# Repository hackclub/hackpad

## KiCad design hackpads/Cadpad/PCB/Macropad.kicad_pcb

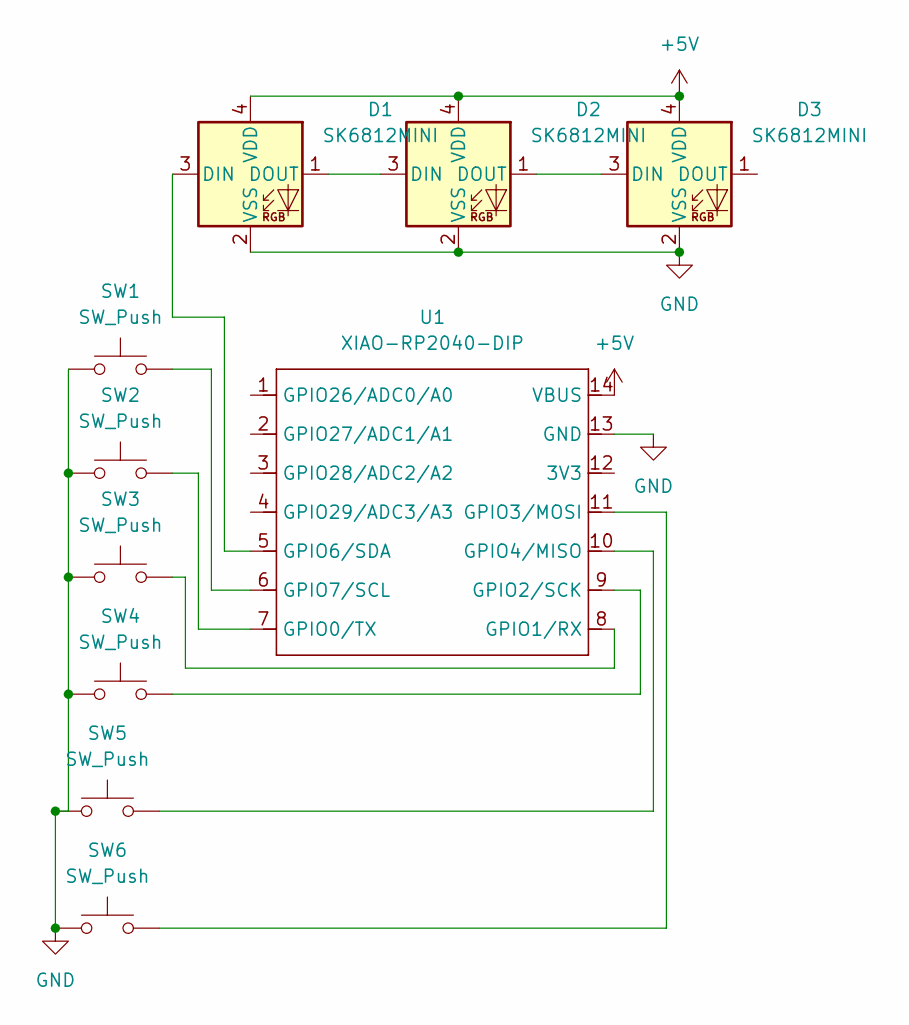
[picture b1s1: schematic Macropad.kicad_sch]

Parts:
D1, D2, D3: SK6812MINI; LED_SK6812MINI_PLCC4_3.5x3.5mm_P1.75mm
SW1, SW2, SW3, SW4, SW5, SW6: SW_Push; SW_Cherry_MX_1.00u_PCB
U1: XIAO-RP2040-DIP

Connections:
+5V: D1.4 (VDD), D2.4 (VDD), D3.4 (VDD), U1.14 (VBUS)
GND: D1.2 (VSS), D2.2 (VSS), D3.2 (VSS), SW1.1, SW2.1, SW3.1, SW4.1, SW5.1, SW6.1, U1.13 (GND)
unnamed: D1.3 (DIN), U1.5 (GPIO6/SDA)
unnamed: D1.1 (DOUT), D2.3 (DIN)
unnamed: D2.1 (DOUT), D3.3 (DIN)
unnamed: SW2.2, U1.7 (GPIO0/TX)
unnamed: SW3.2, U1.8 (GPIO1/RX)
unnamed: SW4.2, U1.9 (GPIO2/SCK)
unnamed: SW6.2, U1.11 (GPIO3/MOSI)
unnamed: SW5.2, U1.10 (GPIO4/MISO)
unnamed: SW1.2, U1.6 (GPIO7/SCL)

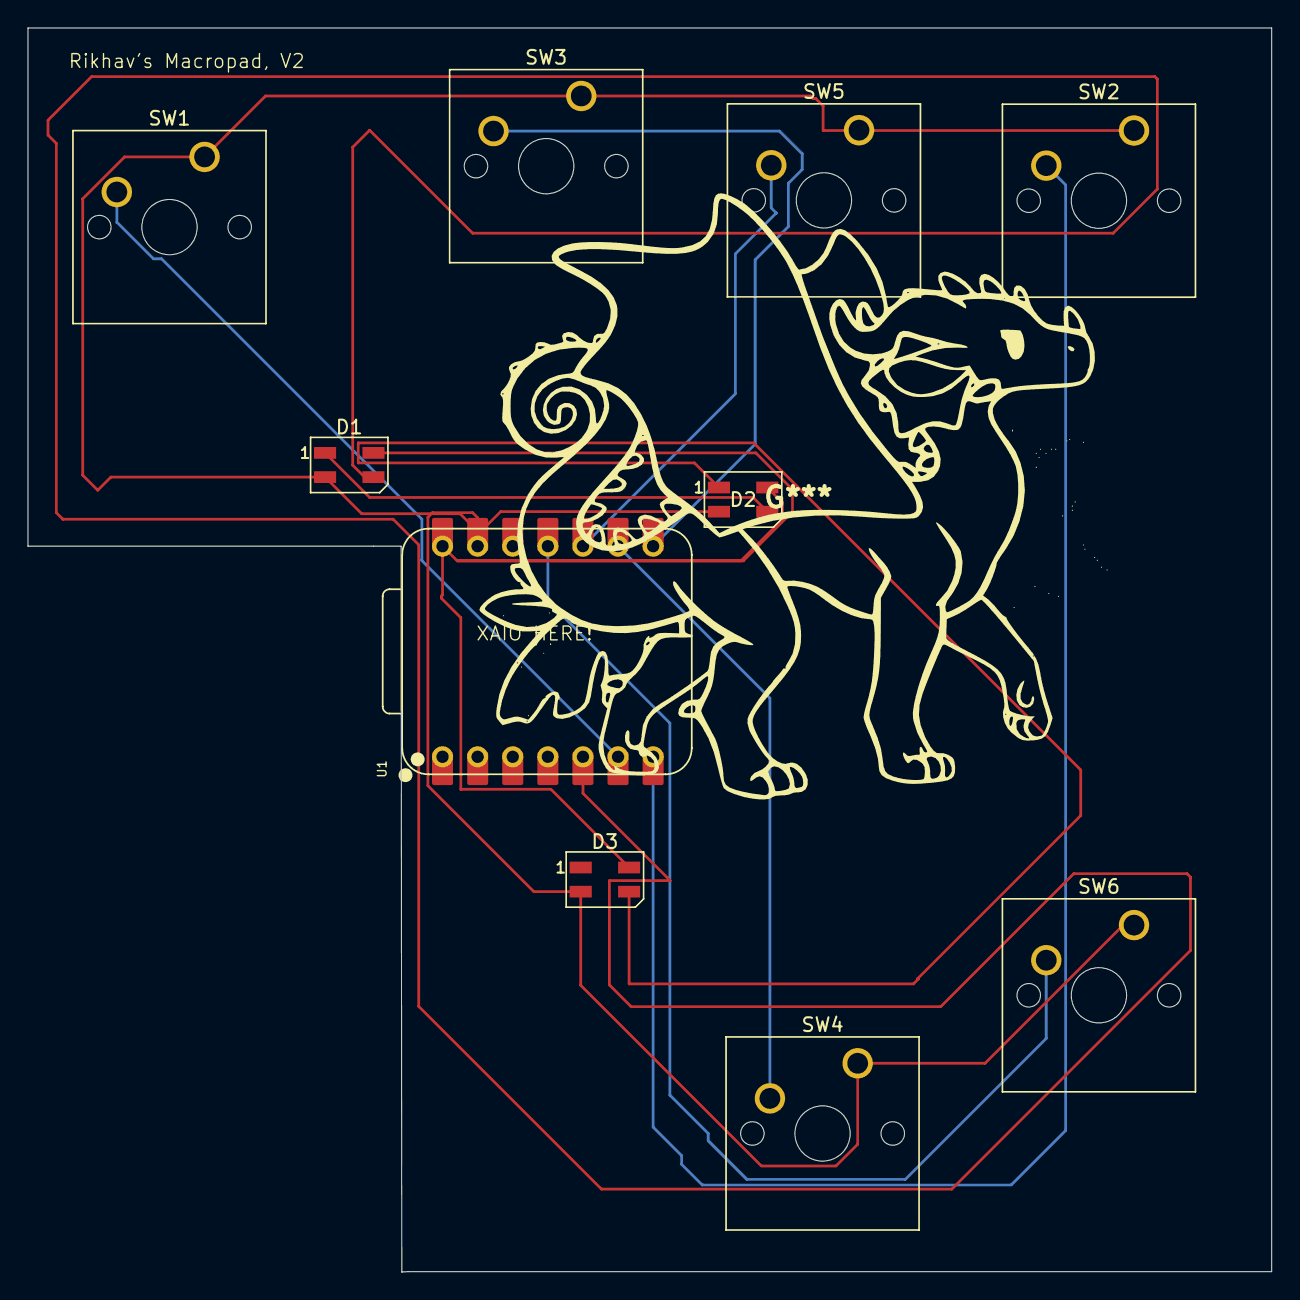
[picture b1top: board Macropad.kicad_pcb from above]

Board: 2 copper layers, 90.0 x 90.0 mm, 10 parts (0 on the bottom side), 11 nets.

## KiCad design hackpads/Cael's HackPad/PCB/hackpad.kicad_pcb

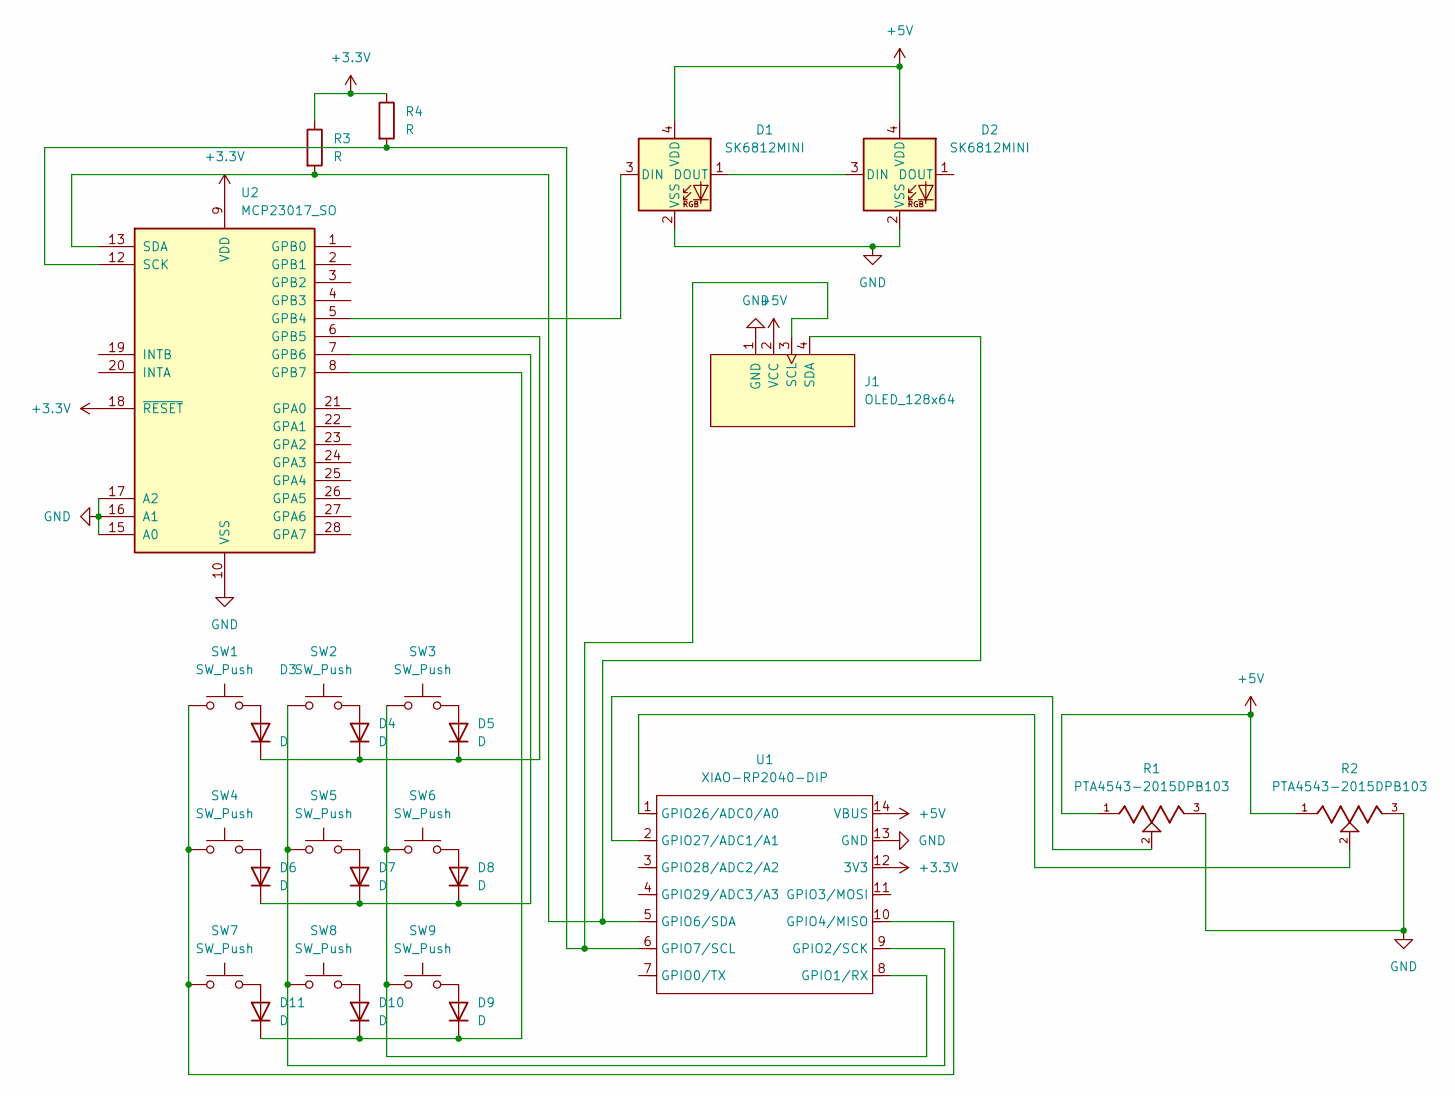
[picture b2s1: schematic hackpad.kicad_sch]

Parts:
D1, D2: SK6812MINI; LED_SK6812MINI_PLCC4_3.5x3.5mm_P1.75mm
D3, D4, D5, D6, D7, D8, D9, D10, D11: D; D_DO-35_SOD27_P7.62mm_Horizontal
J1: OLED_128x64; Adafruit_SSD1306
R1, R2: PTA4543-2015DPB103; BOURNS-PTA4543_45mm-slide-pot; PARTREV 04/21
R3, R4: R; R_Axial_DIN0204_L3.6mm_D1.6mm_P7.62mm_Horizontal
SW1, SW2, SW3, SW4, SW5, SW6, SW7, SW8, SW9: SW_Push; SW_Cherry_MX_1.00u_PCB
U1: XIAO-RP2040-DIP
U2: MCP23017_SO; SOIC-28W_7.5x17.9mm_P1.27mm

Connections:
+3.3V: R3.1, R4.1, U1.12 (3V3), U2.9 (VDD), U2.18 (~RESET)
+5V: D1.4 (VDD), D2.4 (VDD), J1.2 (VCC), R1.1, R2.1, U1.14 (VBUS)
GND: D1.2 (VSS), D2.2 (VSS), J1.1 (GND), R1.3, R2.3, U1.13 (GND), U2.10 (VSS), U2.15 (A0), U2.16 (A1), U2.17 (A2)
unnamed: D1.3 (DIN), U2.5 (GPB4)
unnamed: D1.1 (DOUT), D2.3 (DIN)
unnamed: D3.2 (A), SW1.2
unnamed: D3.1 (K), D4.1 (K), D5.1 (K), U2.6 (GPB5)
unnamed: D4.2 (A), SW2.2
unnamed: D5.2 (A), SW3.2
unnamed: D6.2 (A), SW4.2
unnamed: D6.1 (K), D7.1 (K), D8.1 (K), U2.7 (GPB6)
unnamed: D7.2 (A), SW5.2
unnamed: D8.2 (A), SW6.2
unnamed: D9.2 (A), SW9.2
unnamed: D10.2 (A), SW8.2
unnamed: D9.1 (K), D10.1 (K), D11.1 (K), U2.8 (GPB7)
unnamed: D11.2 (A), SW7.2
unnamed: J1.3 (SCL), R4.2, U1.6 (GPIO7/SCL), U2.12 (SCK)
unnamed: J1.4 (SDA), R3.2, U1.5 (GPIO6/SDA), U2.13 (SDA)
unnamed: SW3.1, SW6.1, SW9.1, U1.8 (GPIO1/RX)
unnamed: SW2.1, SW5.1, SW8.1, U1.9 (GPIO2/SCK)
unnamed: SW1.1, SW4.1, SW7.1, U1.10 (GPIO4/MISO)
unnamed: R2.2, U1.1 (GPIO26/ADC0/A0)
unnamed: R1.2, U1.2 (GPIO27/ADC1/A1)

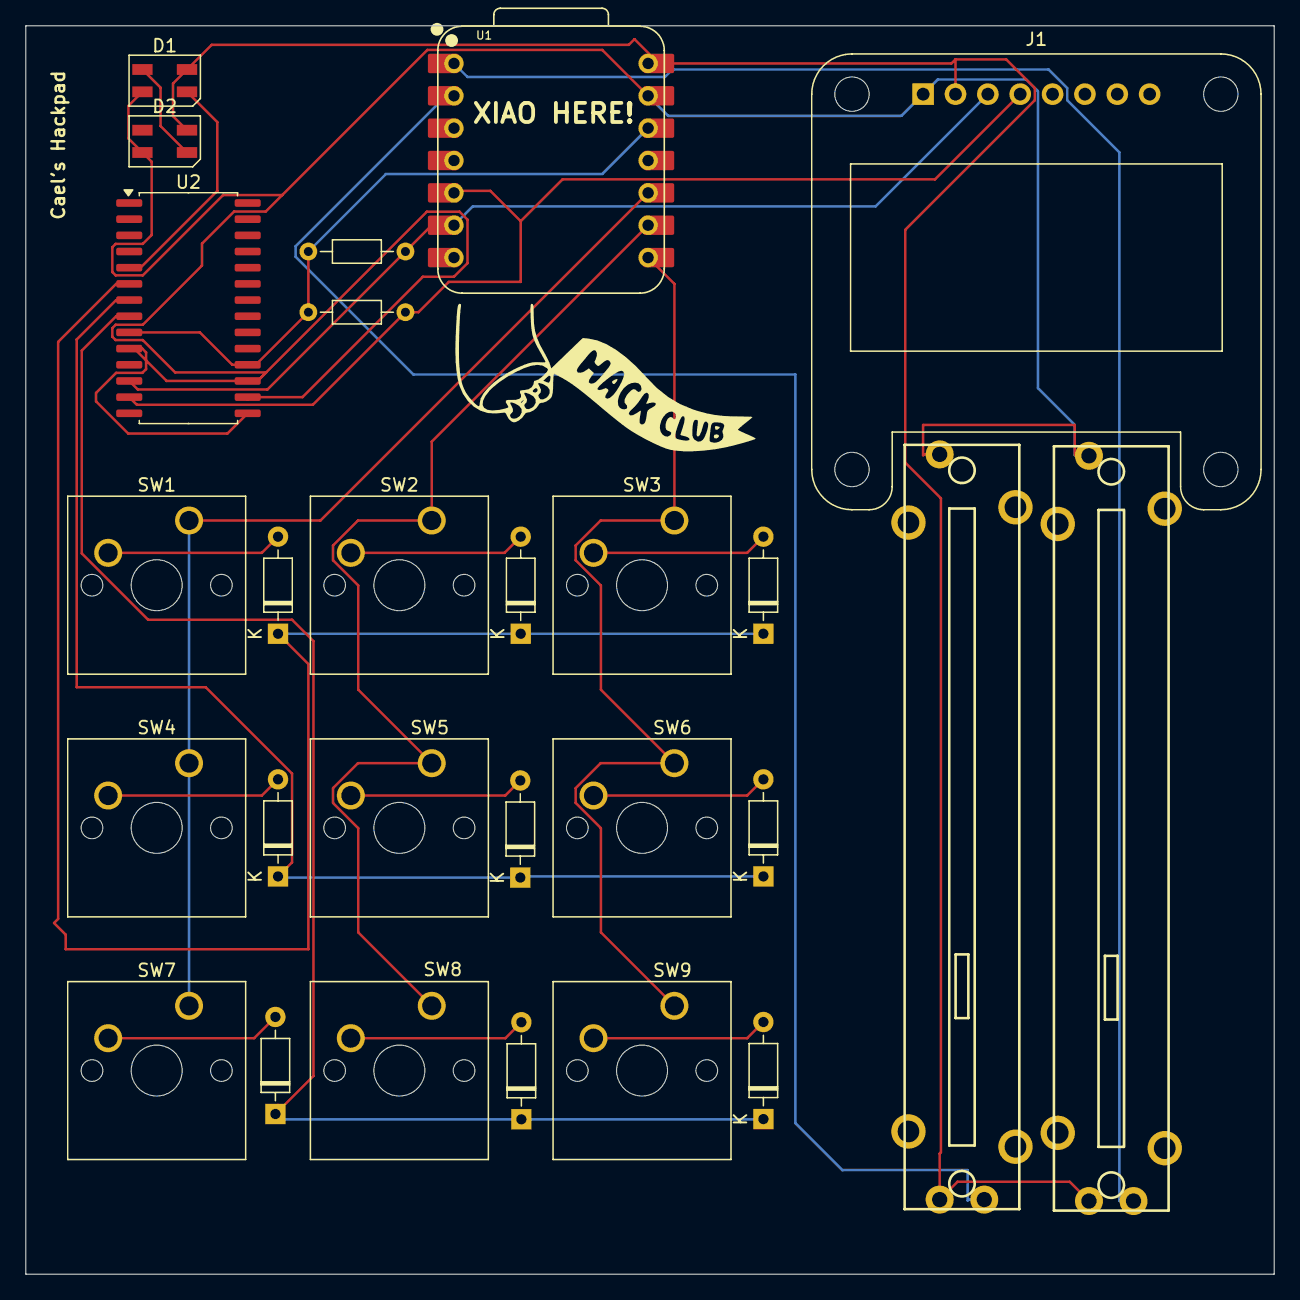
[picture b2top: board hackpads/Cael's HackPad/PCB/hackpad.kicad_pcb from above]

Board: 2 copper layers, 98.0 x 98.0 mm, 27 parts (0 on the bottom side), 24 nets.

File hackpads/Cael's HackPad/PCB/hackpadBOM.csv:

"Reference","Value","Datasheet","Footprint","Qty","DNP"
"D1,D2","SK6812MINI","https://cdn-shop.adafruit.com/product-files/2686/SK6812MINI_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","LED_SMD:LED_SK6812MINI_PLCC4_3.5x3.5mm_P1.75mm","2",""
"D3,D4,D5,D6,D7,D8,D9,D10,D11","D","~","Diode_THT:D_DO-35_SOD27_P7.62mm_Horizontal","9",""
"J1","OLED_128x64","","Display:Adafruit_SSD1306","1",""
"R1,R2","PTA4543-2015DPB103","","SLIDER:BOURNS-PTA4543_45mm-slide-pot","2",""
"R3,R4","R","~","Resistor_THT:R_Axial_DIN0204_L3.6mm_D1.6mm_P7.62mm_Horizontal","2",""
"SW1,SW2,SW3,SW4,SW5,SW6,SW7,SW8,SW9","SW_Push","~","Button_Switch_Keyboard:SW_Cherry_MX_1.00u_PCB","9",""
"U1","XIAO-RP2040-DIP","","OPL:XIAO-RP2040-DIP","1",""
"U2","MCP23017_SO","https://ww1.microchip.com/downloads/aemDocuments/documents/A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","Package_SO:SOIC-28W_7.5x17.9mm_P1.27mm","1",""

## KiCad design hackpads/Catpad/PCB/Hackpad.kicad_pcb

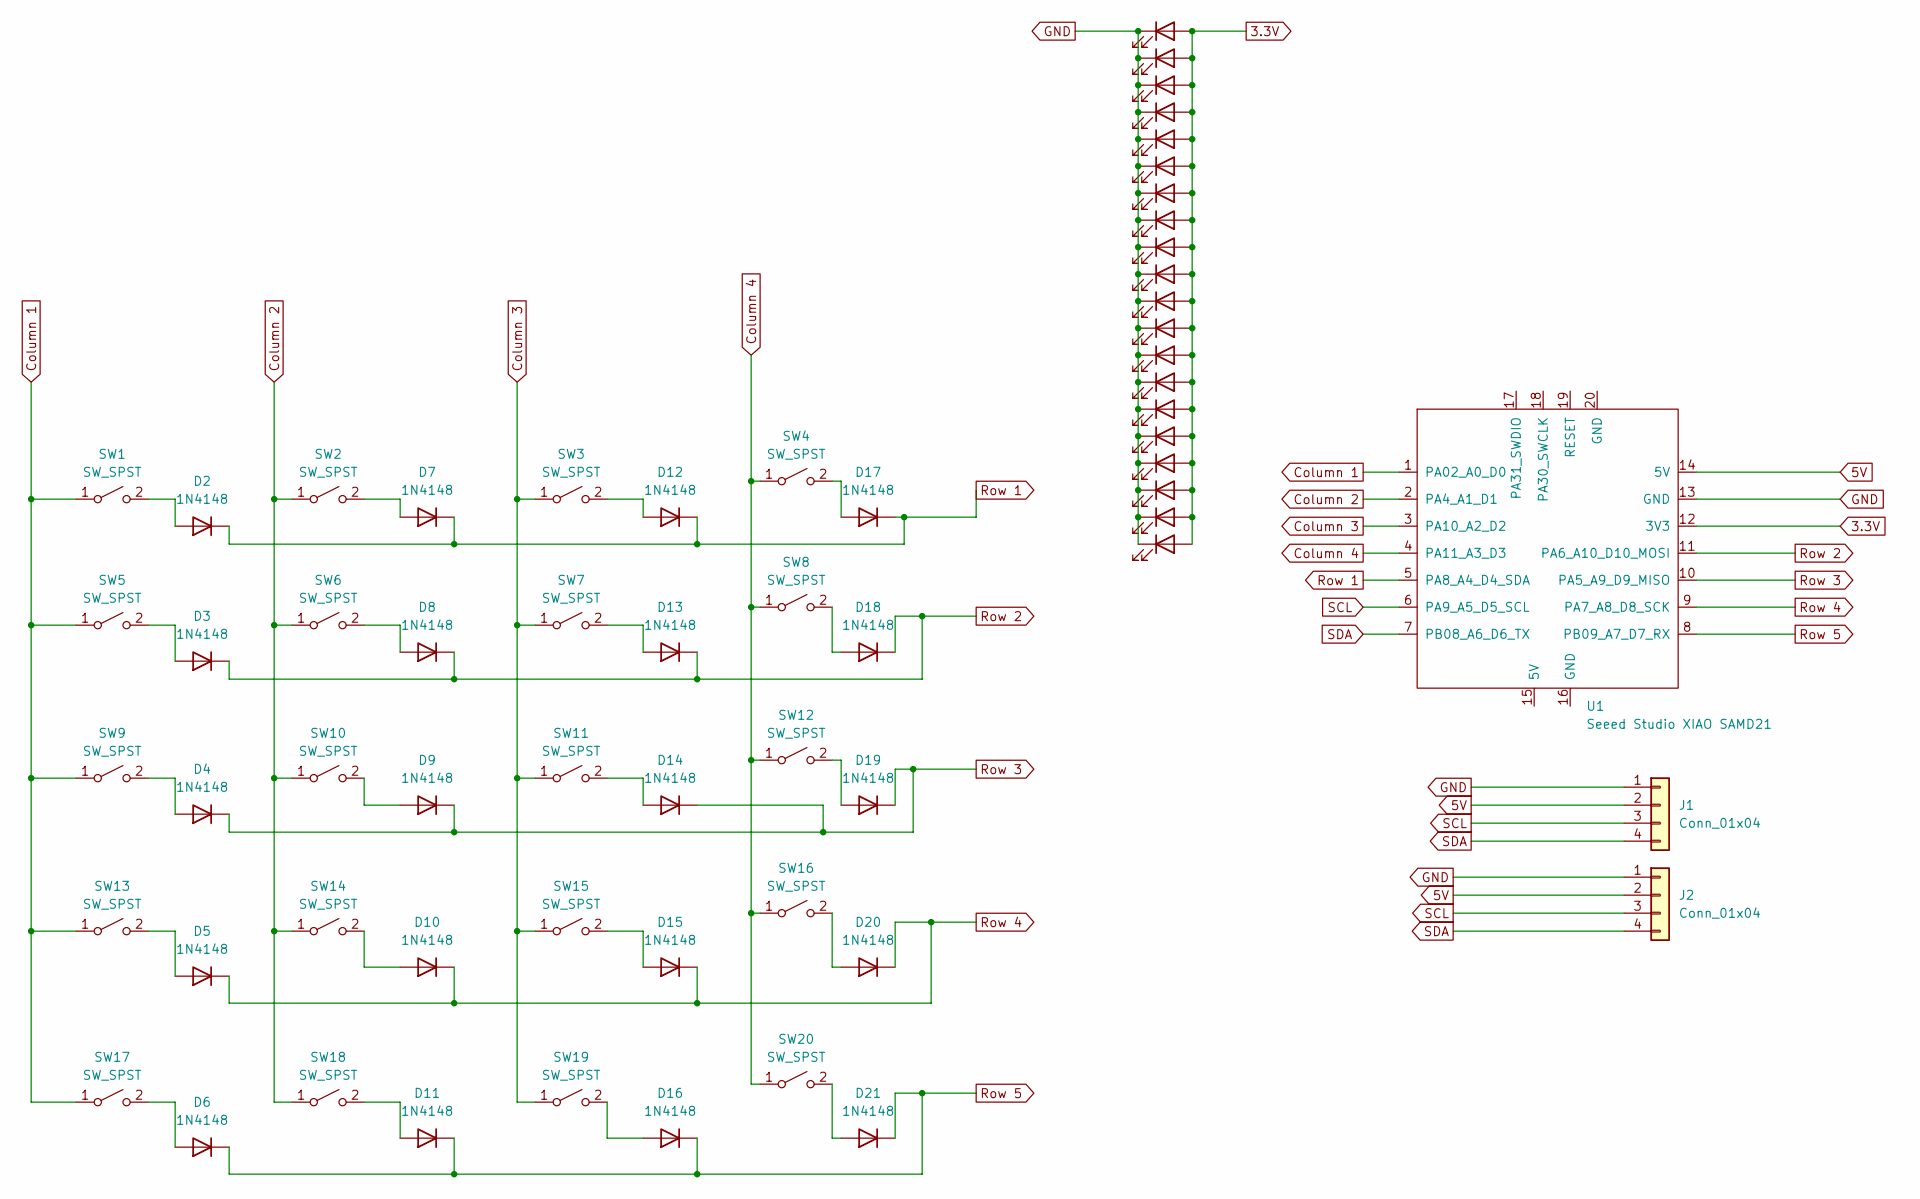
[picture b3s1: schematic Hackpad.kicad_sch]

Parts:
D1, D22, D23, D24, D25, D26, D27, D28, D29, D30, D31, D32, D33, D34, D35, D36, D37, D38, D39, D40: IR26-21C_L110_TR8; LED_1206_3216Metric
D2, D3, D4, D5, D6, D7, D8, D9, D10, D11, D12, D13, D14, D15, D16, D17, D18, D19, D20, D21: 1N4148; D_DO-35_SOD27_P7.62mm_Horizontal
J1, J2: Conn_01x04; SSD1306-0.91-OLED-4pin-128x32
SW1, SW2, SW3, SW4, SW5, SW6, SW7, SW8, SW9, SW10, SW11, SW12, SW13, SW14, SW15, SW16, SW17, SW18, SW19, SW20: SW_SPST; MX-Hotswap-1U
U1: Seeed Studio XIAO SAMD21; XIAO-SAMD21-RP2040-14P-2.54-21X17.8MM (Seeeduino XIAO)

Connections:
3.3V: D1.2 (A), D22.2 (A), D23.2 (A), D24.2 (A), D25.2 (A), D26.2 (A), D27.2 (A), D28.2 (A), D29.2 (A), D30.2 (A), D31.2 (A), D32.2 (A), D33.2 (A), D34.2 (A), D35.2 (A), D36.2 (A), D37.2 (A), D38.2 (A), D39.2 (A), D40.2 (A), U1.12 (3V3)
5V: J1.2, J2.2, U1.14 (5V)
Column 1: SW1.1 (A), SW5.1 (A), SW9.1 (A), SW13.1 (A), SW17.1 (A), U1.1 (PA02_A0_D0)
Column 2: SW2.1 (A), SW6.1 (A), SW10.1 (A), SW14.1 (A), SW18.1 (A), U1.2 (PA4_A1_D1)
Column 3: SW3.1 (A), SW7.1 (A), SW11.1 (A), SW15.1 (A), SW19.1 (A), U1.3 (PA10_A2_D2)
Column 4: SW4.1 (A), SW8.1 (A), SW12.1 (A), SW16.1 (A), SW20.1 (A), U1.4 (PA11_A3_D3)
GND: D1.1 (K), D22.1 (K), D23.1 (K), D24.1 (K), D25.1 (K), D26.1 (K), D27.1 (K), D28.1 (K), D29.1 (K), D30.1 (K), D31.1 (K), D32.1 (K), D33.1 (K), D34.1 (K), D35.1 (K), D36.1 (K), D37.1 (K), D38.1 (K), D39.1 (K), D40.1 (K), J1.1, J2.1, U1.13 (GND)
unnamed: D2.2 (A), SW1.2 (B)
unnamed: D3.2 (A), SW5.2 (B)
unnamed: D4.2 (A), SW9.2 (B)
unnamed: D5.2 (A), SW13.2 (B)
unnamed: D6.2 (A), SW17.2 (B)
unnamed: D7.2 (A), SW2.2 (B)
unnamed: D8.2 (A), SW6.2 (B)
unnamed: D9.2 (A), SW10.2 (B)
unnamed: D10.2 (A), SW14.2 (B)
unnamed: D11.2 (A), SW18.2 (B)
unnamed: D12.2 (A), SW3.2 (B)
unnamed: D13.2 (A), SW7.2 (B)
unnamed: D14.2 (A), SW11.2 (B)
unnamed: D15.2 (A), SW15.2 (B)
unnamed: D16.2 (A), SW19.2 (B)
unnamed: D17.2 (A), SW4.2 (B)
unnamed: D18.2 (A), SW8.2 (B)
unnamed: D19.2 (A), SW12.2 (B)
unnamed: D20.2 (A), SW16.2 (B)
unnamed: D21.2 (A), SW20.2 (B)
Row 1: D2.1 (K), D7.1 (K), D12.1 (K), D17.1 (K), U1.5 (PA8_A4_D4_SDA)
Row 2: D3.1 (K), D8.1 (K), D13.1 (K), D18.1 (K), U1.11 (PA6_A10_D10_MOSI)
Row 3: D4.1 (K), D9.1 (K), D14.1 (K), D19.1 (K), U1.10 (PA5_A9_D9_MISO)
Row 4: D5.1 (K), D10.1 (K), D15.1 (K), D20.1 (K), U1.9 (PA7_A8_D8_SCK)
Row 5: D6.1 (K), D11.1 (K), D16.1 (K), D21.1 (K), U1.8 (PB09_A7_D7_RX)
SCL: J1.3, J2.3, U1.6 (PA9_A5_D5_SCL)
SDA: J1.4, J2.4, U1.7 (PB08_A6_D6_TX)

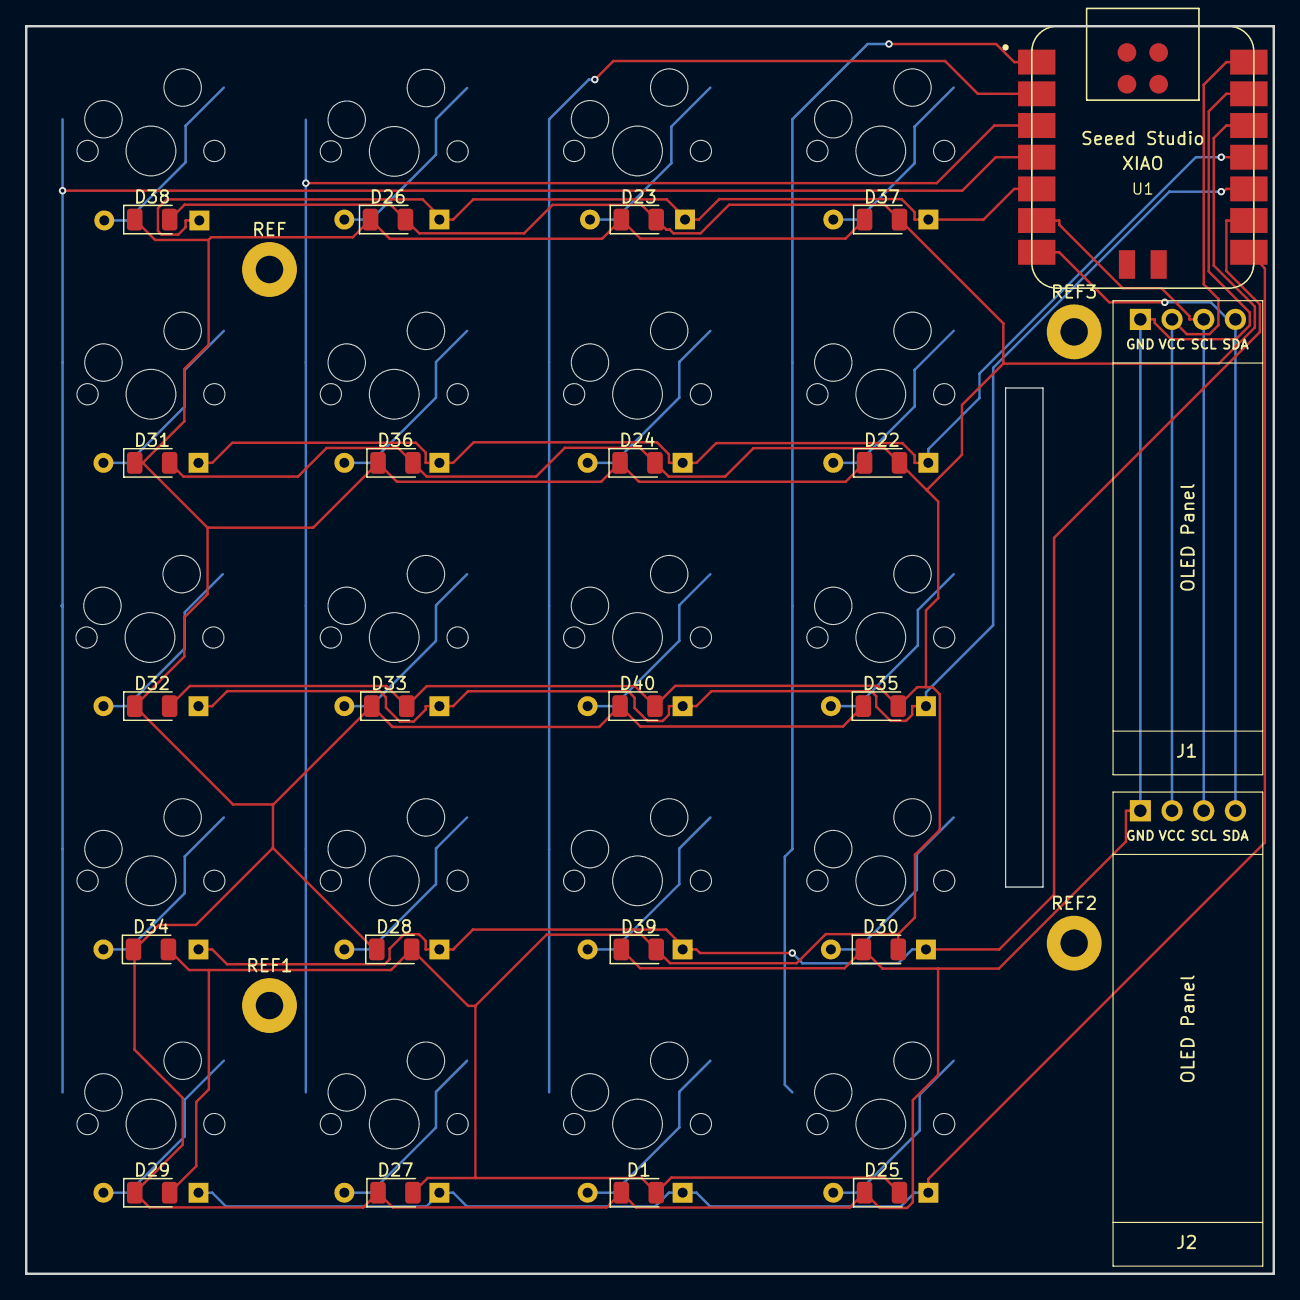
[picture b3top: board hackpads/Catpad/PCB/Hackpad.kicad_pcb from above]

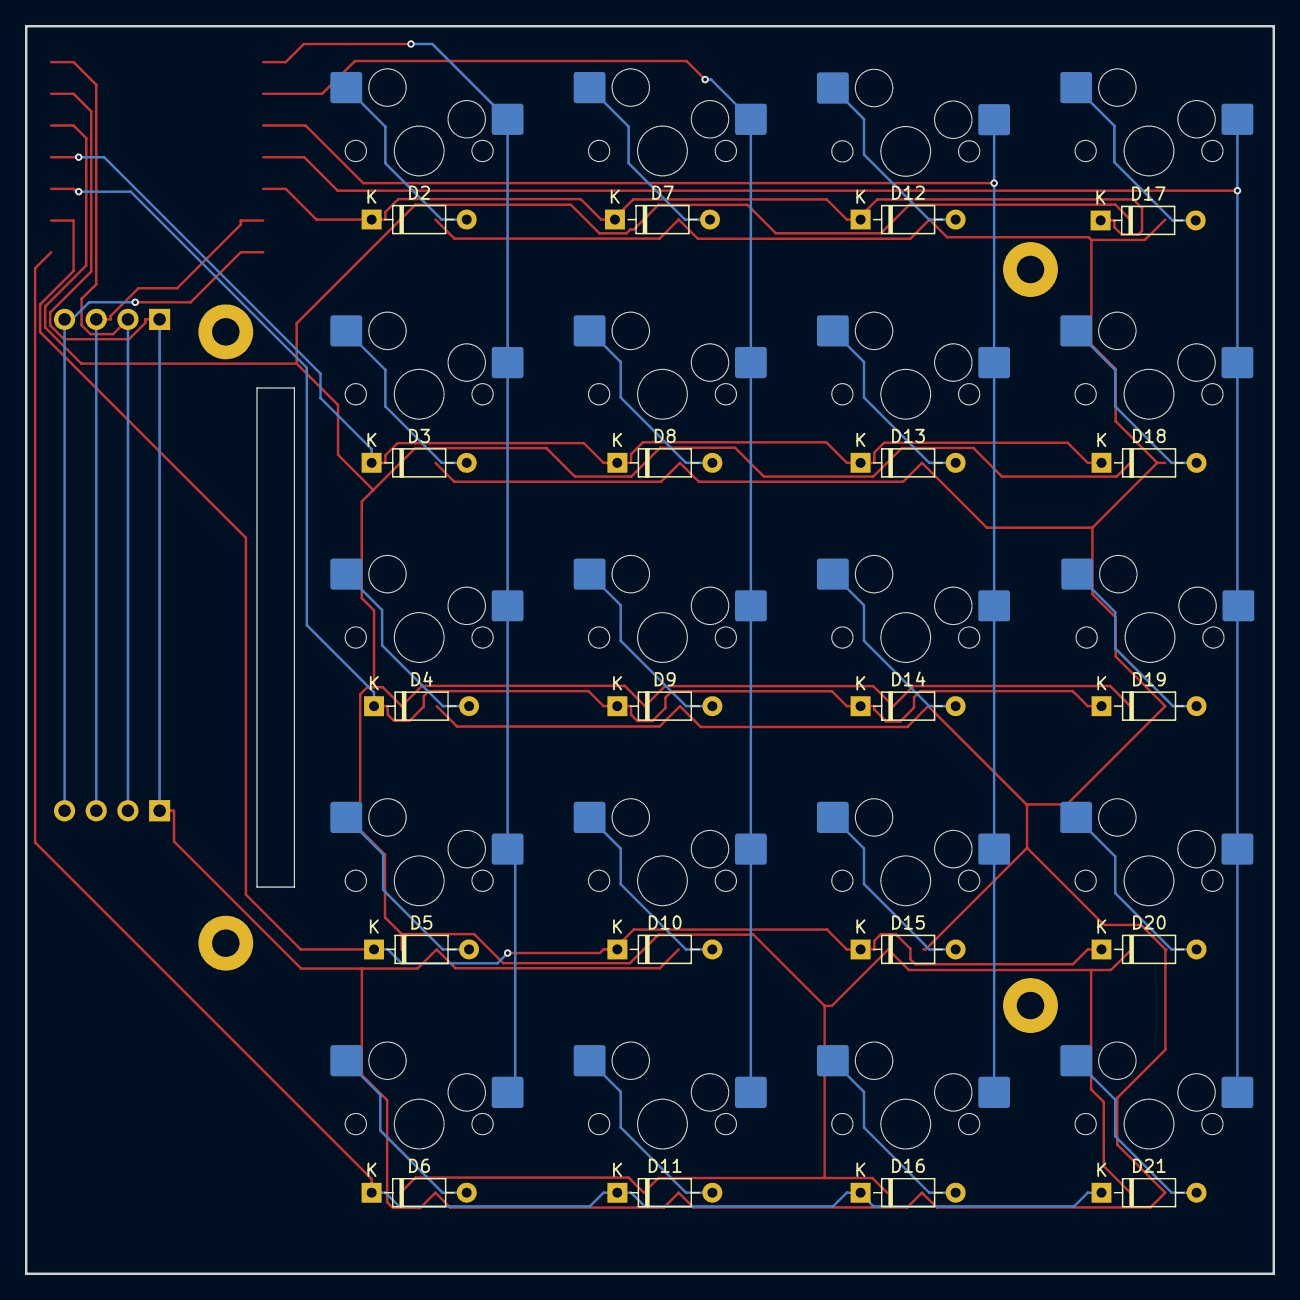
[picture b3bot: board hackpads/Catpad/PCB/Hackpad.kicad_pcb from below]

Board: 2 copper layers, 100.0 x 100.0 mm, 67 parts (40 on the bottom side), 34 nets.

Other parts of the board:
REF, REF1, REF2, REF3: MountingHole_2.2mm_M2_Pad

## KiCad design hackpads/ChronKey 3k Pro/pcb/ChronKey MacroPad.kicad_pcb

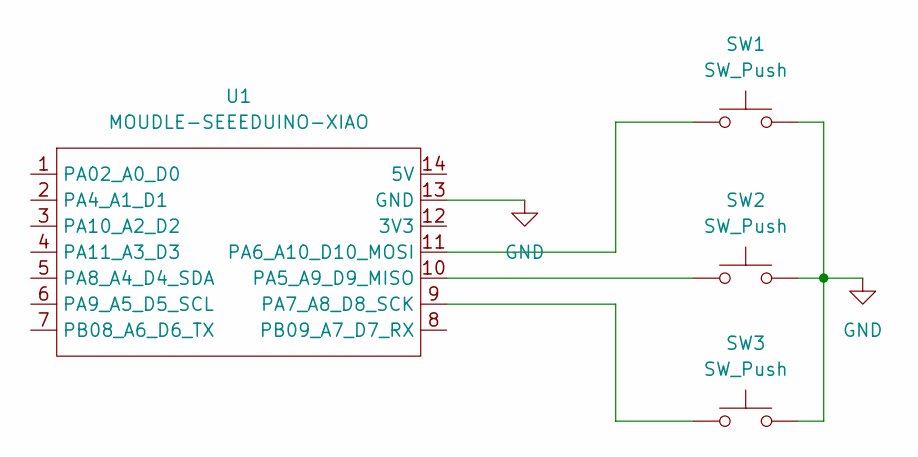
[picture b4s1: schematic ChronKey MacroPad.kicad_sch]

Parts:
SW1, SW2, SW3: SW_Push; SW_Cherry_MX_1.00u_PCB
U1: MOUDLE-SEEEDUINO-XIAO; XIAO-Generic-Hybrid-14P-2.54-21X17.8MM

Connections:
GND: SW1.2, SW2.2, SW3.2, U1.13 (GND)
unnamed: SW2.1, U1.10 (PA5_A9_D9_MISO)
unnamed: SW1.1, U1.11 (PA6_A10_D10_MOSI)
unnamed: SW3.1, U1.9 (PA7_A8_D8_SCK)

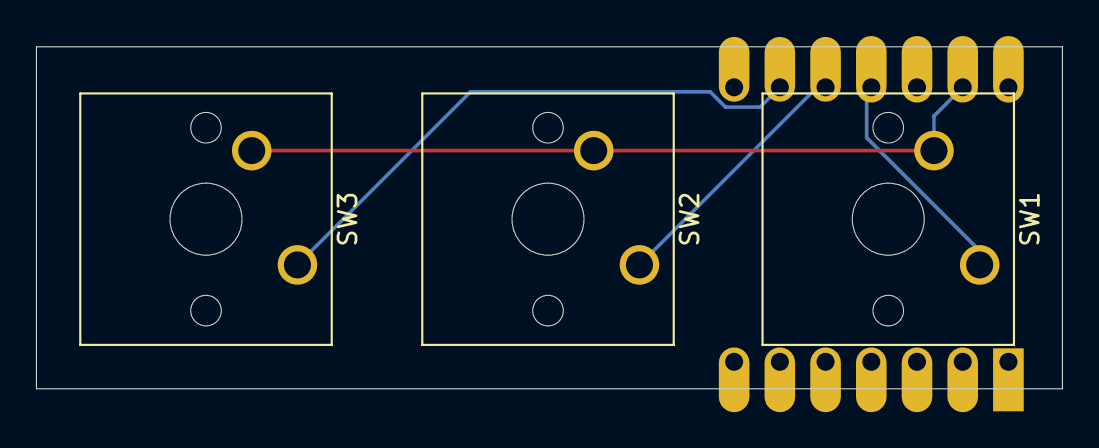
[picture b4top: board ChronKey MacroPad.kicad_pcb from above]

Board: 2 copper layers, 57.0 x 19.0 mm, 4 parts (1 on the bottom side), 4 nets.

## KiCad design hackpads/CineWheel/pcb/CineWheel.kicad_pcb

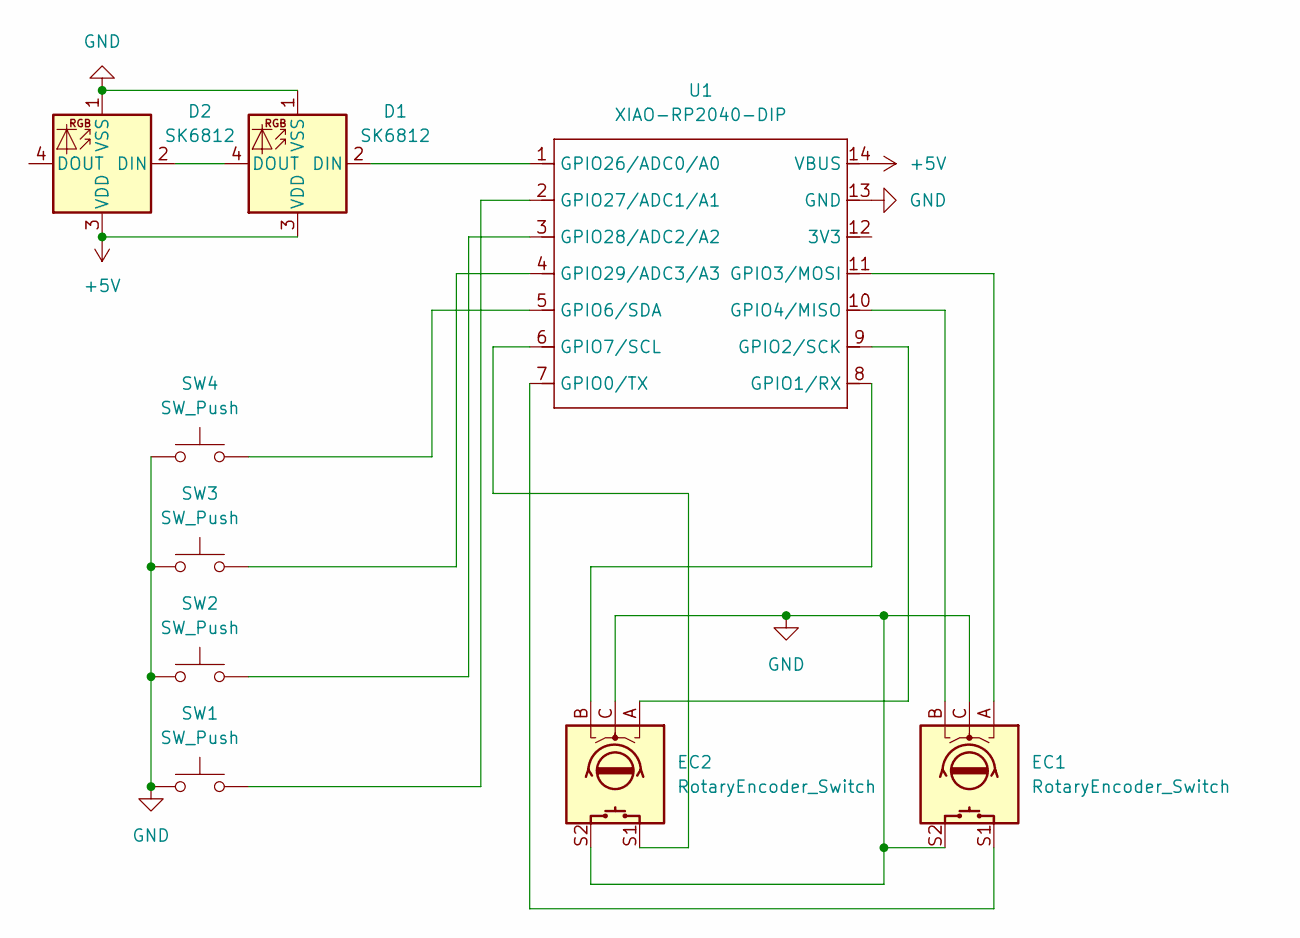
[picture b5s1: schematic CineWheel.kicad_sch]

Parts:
D1, D2: SK6812; LED_SK6812_PLCC4_5.0x5.0mm_P3.2mm
EC1, EC2: RotaryEncoder_Switch; RotaryEncoder_Alps_EC11E-Switch_Vertical_H20mm
SW1, SW2, SW3, SW4: SW_Push; SW_Cherry_MX_1.00u_PCB
U1: XIAO-RP2040-DIP; XIAO-RP2040-SMD

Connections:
+5V: D1.3 (VDD), D2.3 (VDD), U1.14 (VBUS)
GND: D1.1 (VSS), D2.1 (VSS), EC1.C, EC1.S2, EC2.C, EC2.S2, SW1.1, SW2.1, SW3.1, SW4.1, U1.13 (GND)
unnamed: D1.2 (DIN), U1.1 (GPIO26/ADC0/A0)
unnamed: D1.4 (DOUT), D2.2 (DIN)
unnamed: EC1.S1, U1.7 (GPIO0/TX)
unnamed: EC2.B, U1.8 (GPIO1/RX)
unnamed: EC2.A, U1.9 (GPIO2/SCK)
unnamed: EC1.A, U1.11 (GPIO3/MOSI)
unnamed: EC1.B, U1.10 (GPIO4/MISO)
unnamed: SW4.2, U1.5 (GPIO6/SDA)
unnamed: EC2.S1, U1.6 (GPIO7/SCL)
unnamed: SW1.2, U1.2 (GPIO27/ADC1/A1)
unnamed: SW2.2, U1.3 (GPIO28/ADC2/A2)
unnamed: SW3.2, U1.4 (GPIO29/ADC3/A3)

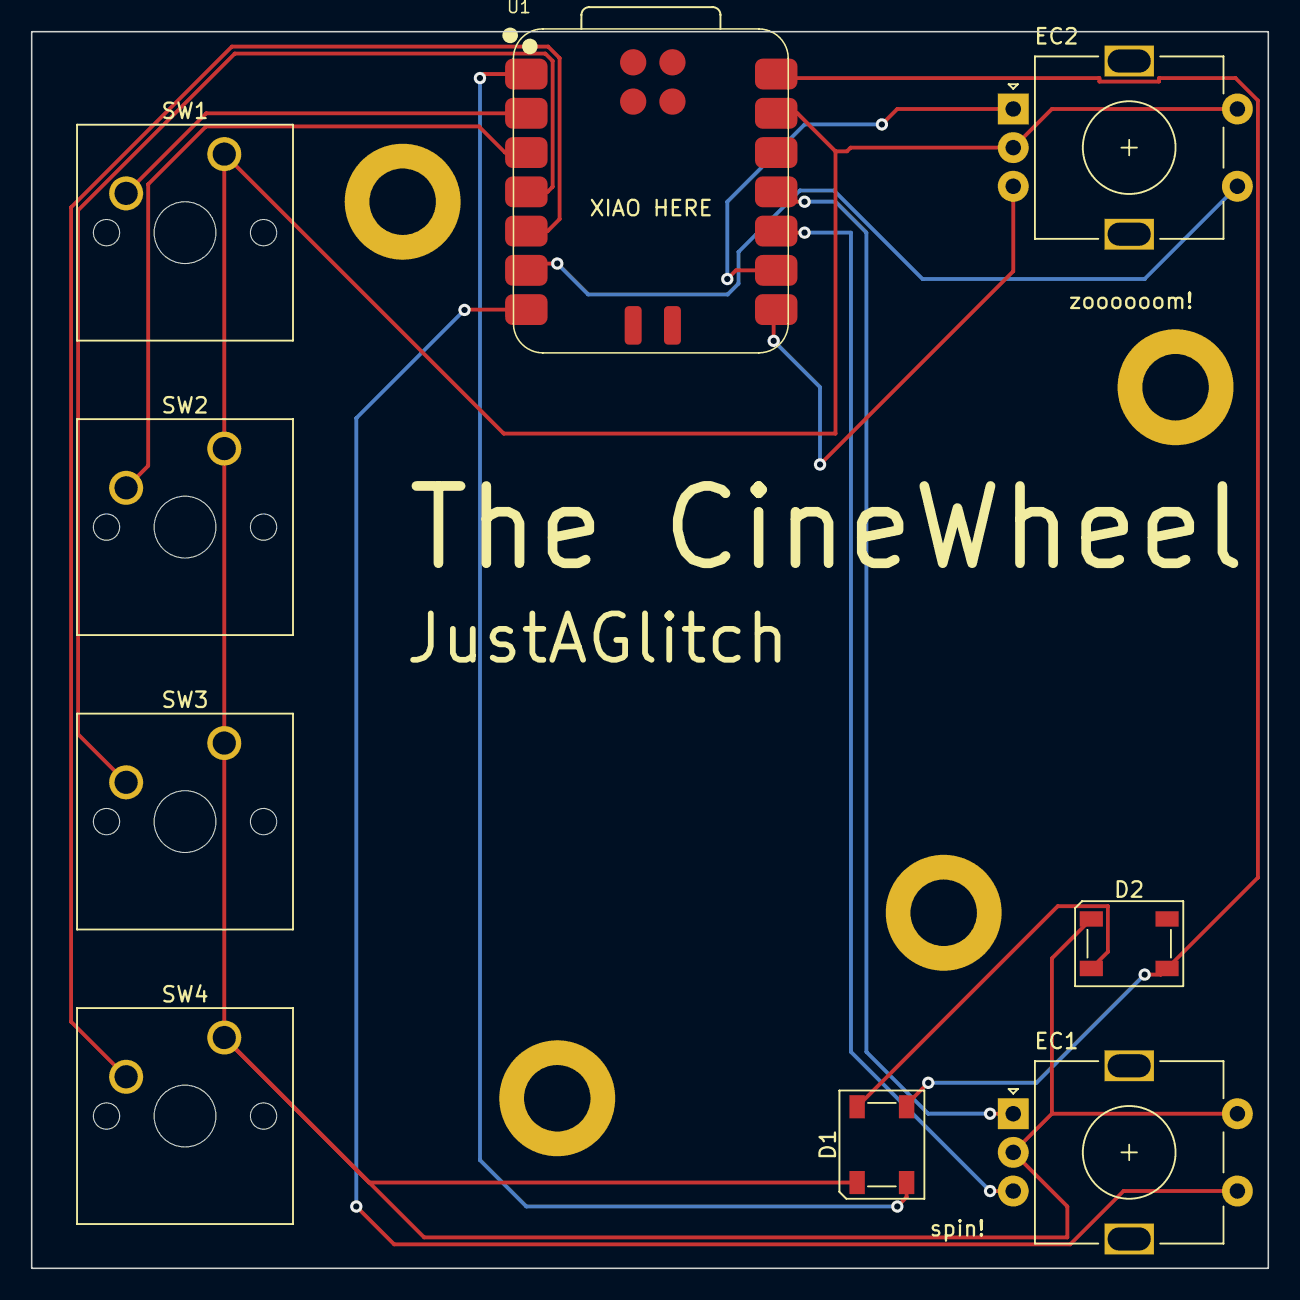
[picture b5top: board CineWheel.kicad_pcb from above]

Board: 2 copper layers, 80.0 x 80.0 mm, 9 parts (0 on the bottom side), 14 nets.

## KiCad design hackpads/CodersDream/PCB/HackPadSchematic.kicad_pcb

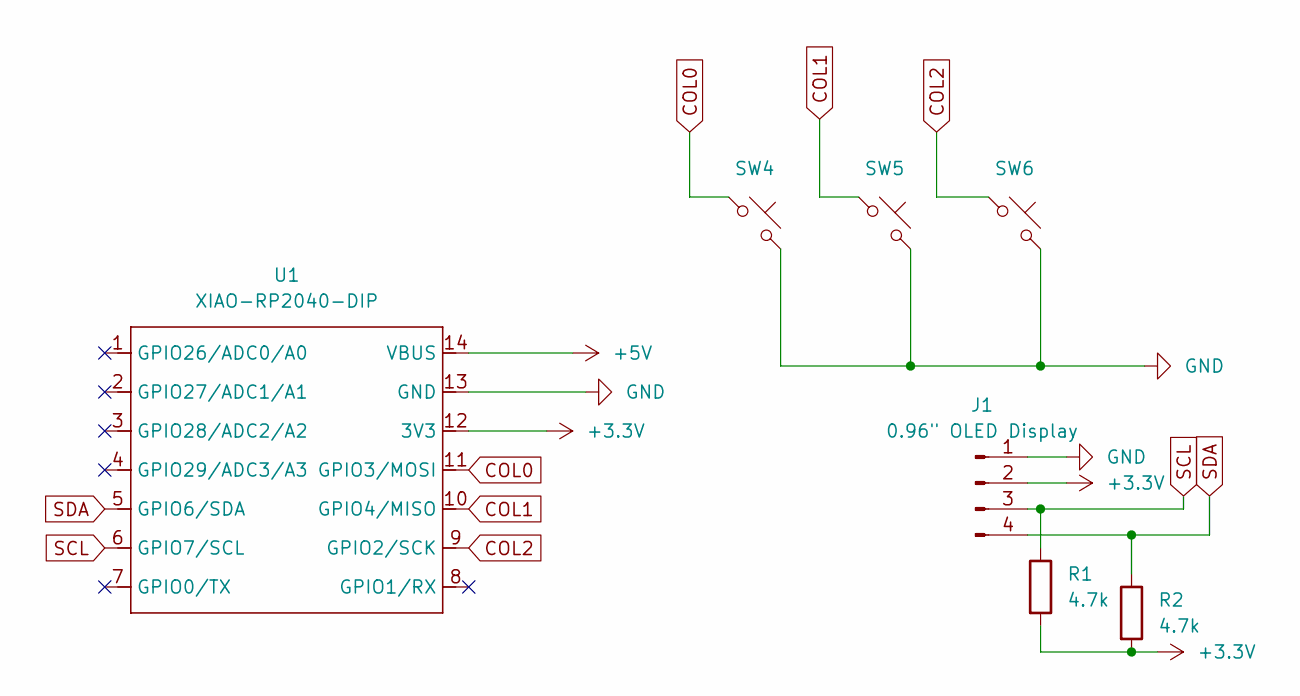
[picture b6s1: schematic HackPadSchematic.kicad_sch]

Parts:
J1: 0.96" OLED Display; MODULE_DM-OLED096-636
R1, R2: 4.7k; R_Axial_DIN0204_L3.6mm_D1.6mm_P5.08mm_Horizontal
SW4, SW5, SW6: MX; SW_Cherry_MX_1.00u_PCB
U1: XIAO-RP2040-DIP

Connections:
+3.3V: J1.2, R1.2, R2.2, U1.12 (3V3)
+5V: U1.14 (VBUS)
COL0: SW4.1, U1.11 (GPIO3/MOSI)
COL1: SW5.1, U1.10 (GPIO4/MISO)
COL2: SW6.1, U1.9 (GPIO2/SCK)
GND: J1.1, SW4.2, SW5.2, SW6.2, U1.13 (GND)
SCL: J1.3, R1.1, U1.6 (GPIO7/SCL)
SDA: J1.4, R2.1, U1.5 (GPIO6/SDA)
